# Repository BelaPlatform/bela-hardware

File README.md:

# Bela Hardware

This repo contains the editable hardware design files for Bela products, including Bela, Bela Mini, Bela accessories.

These PCB designs have been created in and are editable with Cadsoft EAGLE (https://cadsoft.io) and Kicad (http://kicad.org). 

## Licensing

The hardware designs in this repo are licensed under a Creative Commons Attribution Sharealike license, or [CC-BY-SA](http://creativecommons.org/licenses/by-sa/3.0/). This means you are free edit and use these designs, as long as you agree to supply credit and release your results under the same license. [Read about CC-BY-SA here](http://creativecommons.org/licenses/by-sa/3.0/).

If you want to create a commercial product using the Bela hardware designs and don't want to release it under the same license, you will need a commercial license. Drop us an email at info@bela.io to discuss your project, and we can suggest a commercial license to fit your project's scope and scale.

## Branding

The Bela logo is copyrighted, and is reserved for products made or licensed by the Bela team. If you want to include a Bela logo on your project, we've made a Made With Bela logo just for this. [See this page for details on logo use](https://belaplatform.github.io/bela_sample/src/#logos) and to download the Made With Bela logo.

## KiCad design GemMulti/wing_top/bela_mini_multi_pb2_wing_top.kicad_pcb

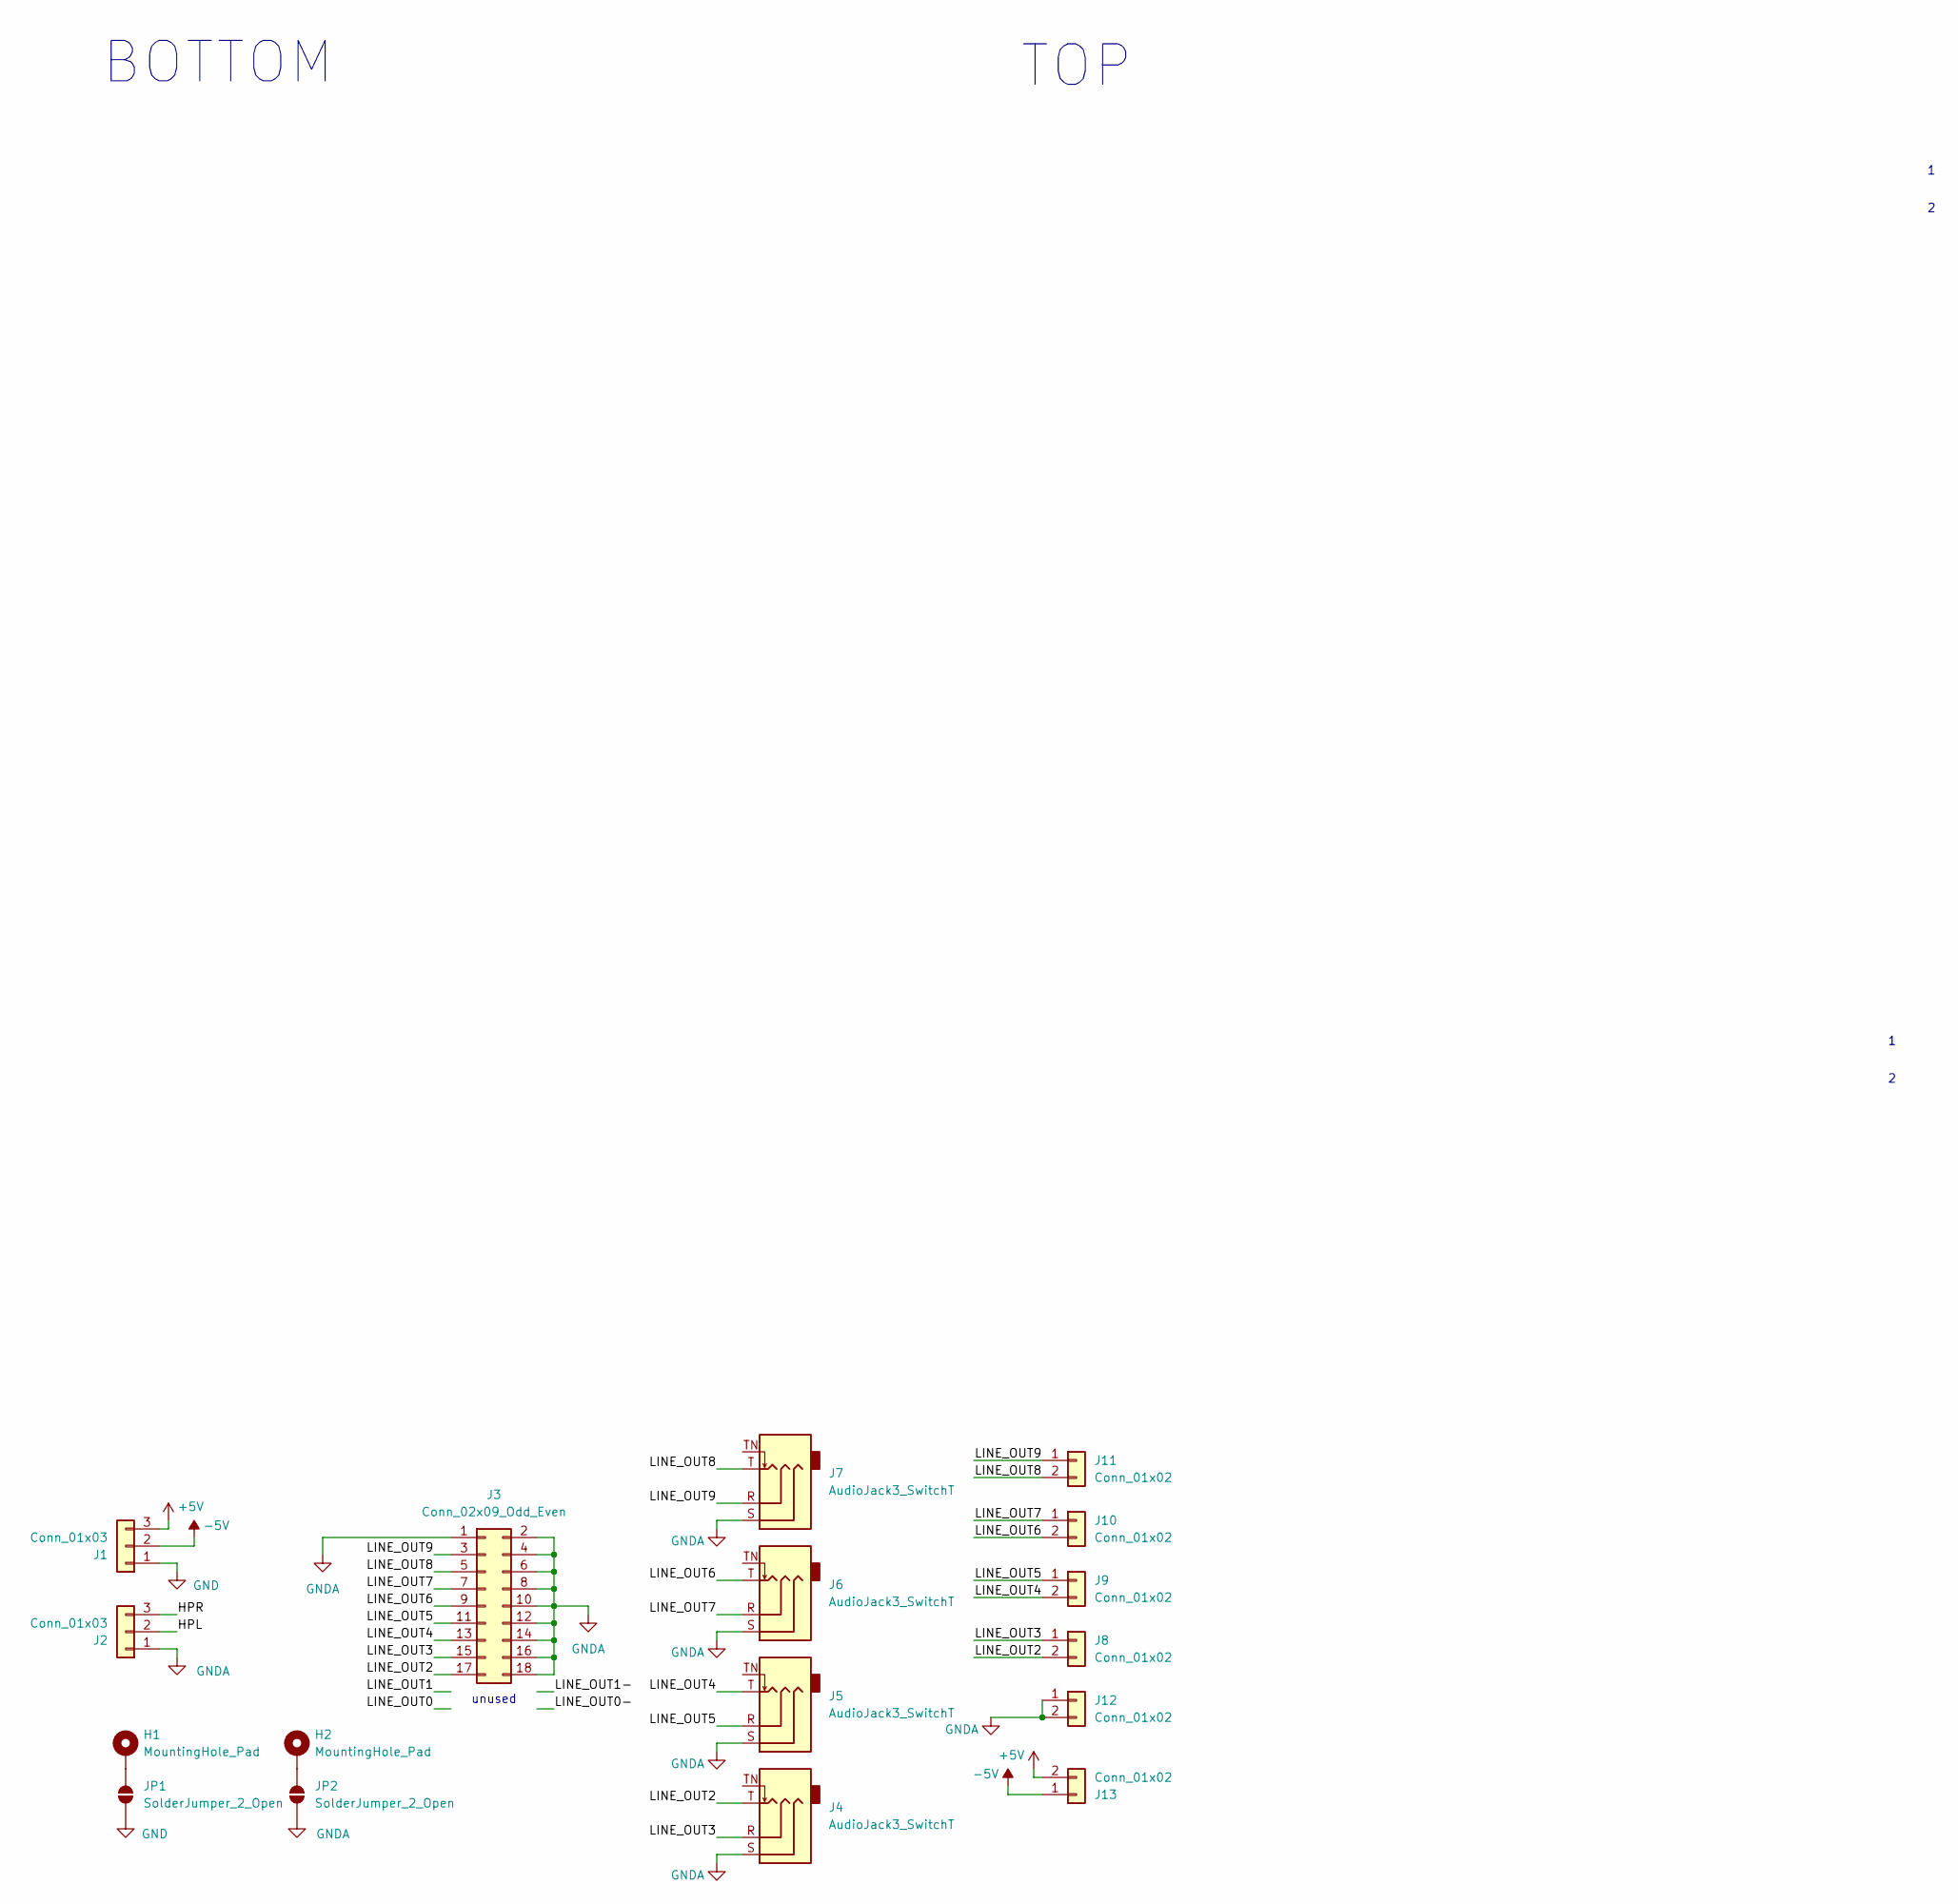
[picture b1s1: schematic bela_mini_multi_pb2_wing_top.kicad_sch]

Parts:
H1, H2: MountingHole_Pad; MountingHole_3.2mm_M3_DIN965_Pad
J1, J2: Conn_01x03; PinHeader_1x03_P2.54mm_Vertical
J3: Conn_02x09_Odd_Even; PinHeader_2x09_P2.54mm_Vertical_SMD
J4, J5, J6, J7: AudioJack3_SwitchT; Jack_3.5mm_SameSky_SJ235813BSMTTR
J8, J9, J10, J11, J12, J13: Conn_01x02; PinSocket_1x02_P2.54mm_Vertical
JP1, JP2: SolderJumper_2_Open; SolderJumper-2_P1.3mm_Open_RoundedPad1.0x1.5mm

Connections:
+5V: J1.3, J13.2
-5V: J1.2, J13.1
/HPL: J2.2
/HPR: J2.3
/LINE_OUT2: J3.17, J4.T, J8.2
/LINE_OUT3: J3.15, J4.R, J8.1
/LINE_OUT4: J3.13, J5.T, J9.2
/LINE_OUT5: J3.11, J5.R, J9.1
/LINE_OUT6: J3.9, J6.T, J10.2
/LINE_OUT7: J3.7, J6.R, J10.1
/LINE_OUT8: J3.5, J7.T, J11.2
/LINE_OUT9: J3.3, J7.R, J11.1
GND: J1.1, JP1.1 (A)
GNDA: J2.1, J3.1, J3.2, J3.4, J3.6, J3.8, J3.10, J3.12, J3.14, J3.16, J3.18, J4.S, J5.S, J6.S, J7.S, J12.1, J12.2, JP2.1 (A)
unnamed: H1.1, JP1.2 (B)
unnamed: H2.1, JP2.2 (B)

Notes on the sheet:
unused
BOTTOM
TOP

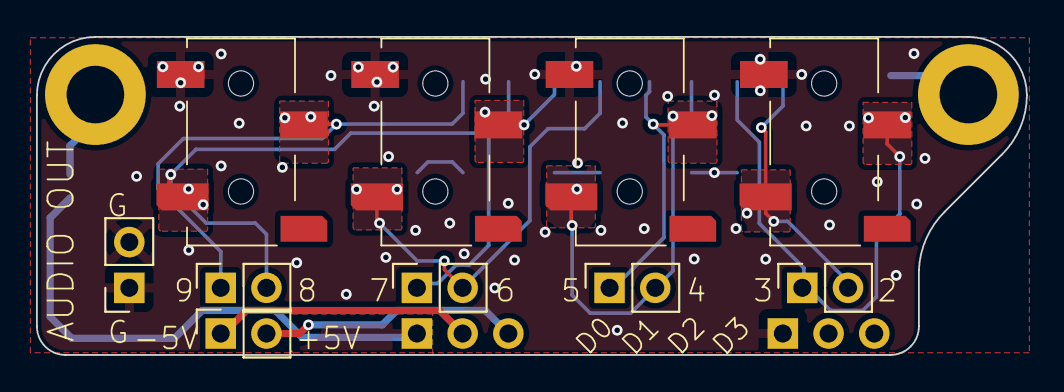
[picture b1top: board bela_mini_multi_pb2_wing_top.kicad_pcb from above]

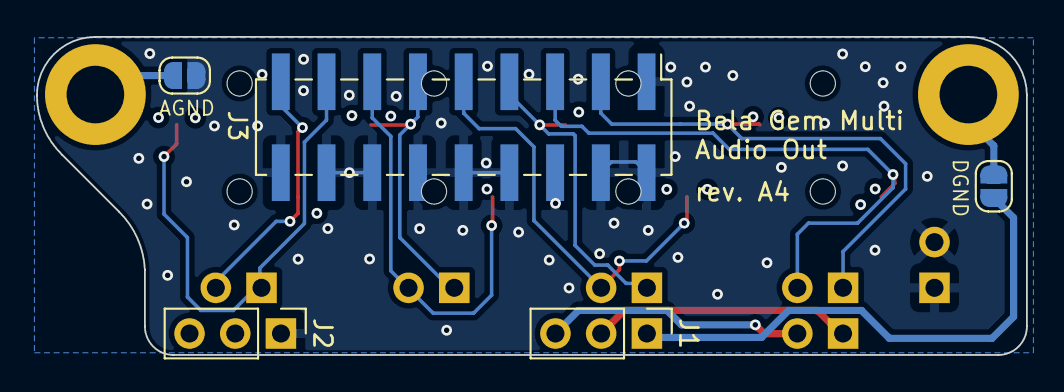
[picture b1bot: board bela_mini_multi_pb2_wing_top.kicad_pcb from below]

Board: 2 copper layers, 55.0 x 17.7 mm, 17 parts (5 on the bottom side), 14 nets.

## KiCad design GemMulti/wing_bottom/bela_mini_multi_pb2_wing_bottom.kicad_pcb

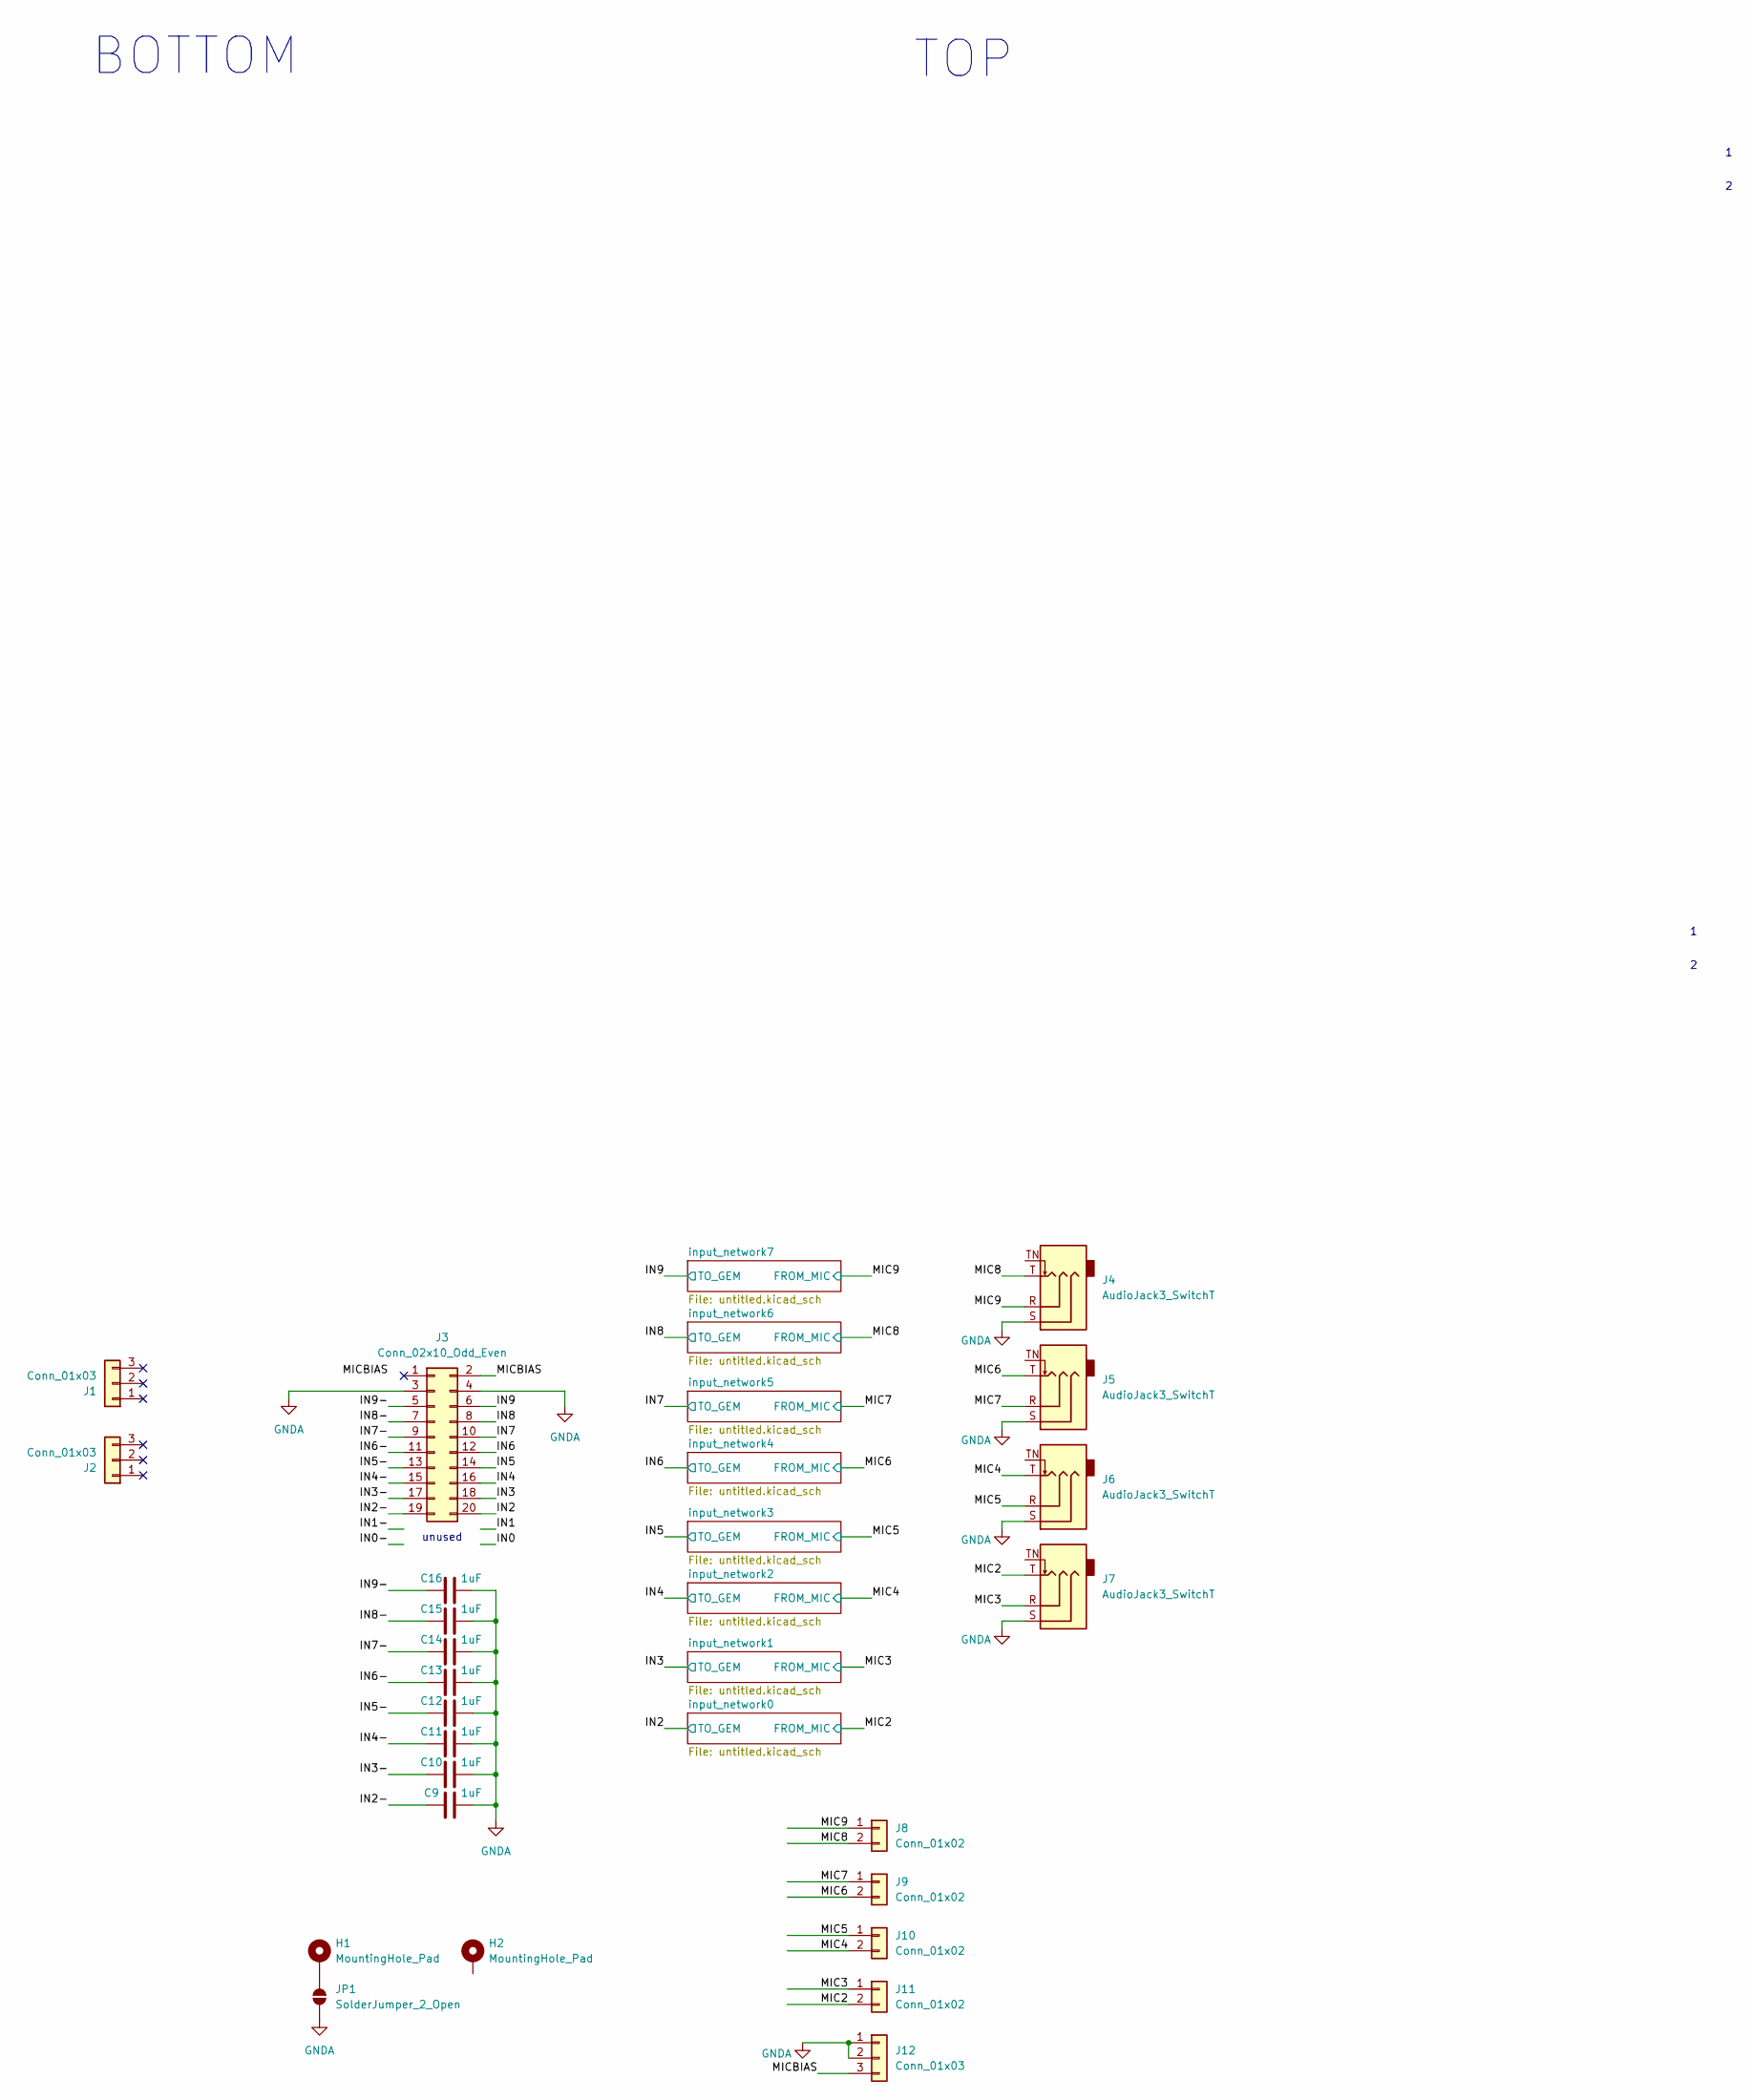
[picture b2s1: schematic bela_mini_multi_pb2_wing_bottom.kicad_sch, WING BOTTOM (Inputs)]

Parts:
C9, C10, C11, C12, C13, C14, C15, C16: 1uF; C_0402_1005Metric
H1, H2: MountingHole_Pad; MountingHole_3.2mm_M3_DIN965_Pad
J1, J2: Conn_01x03; PinHeader_1x03_P2.54mm_Vertical
J3: Conn_02x10_Odd_Even; PinHeader_2x10_P2.54mm_Vertical_SMD
J4, J5, J6, J7: AudioJack3_SwitchT; Jack_3.5mm_SameSky_SJ235813BSMTTR
J8, J9, J10, J11: Conn_01x02; PinSocket_1x02_P2.54mm_Vertical
J12: Conn_01x03; PinSocket_1x03_P2.54mm_Vertical
JP1: SolderJumper_2_Open; SolderJumper-2_P1.3mm_Open_RoundedPad1.0x1.5mm

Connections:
/IN2: J3.20; also elsewhere on the board
/IN2-: C9.1, J3.19
/IN3: J3.18; also elsewhere on the board
/IN3-: C10.1, J3.17
/IN4: J3.16; also elsewhere on the board
/IN4-: C11.1, J3.15
/IN5: J3.14; also elsewhere on the board
/IN5-: C12.1, J3.13
/IN6: J3.12; also elsewhere on the board
/IN6-: C13.1, J3.11
/IN7: J3.10; also elsewhere on the board
/IN7-: C14.1, J3.9
/IN8: J3.8; also elsewhere on the board
/IN8-: C15.1, J3.7
/IN9: J3.6; also elsewhere on the board
/IN9-: C16.1, J3.5
/MIC2: J7.T, J11.2; also elsewhere on the board
/MIC3: J7.R, J11.1; also elsewhere on the board
/MIC4: J6.T, J10.2; also elsewhere on the board
/MIC5: J6.R, J10.1; also elsewhere on the board
/MIC6: J5.T, J9.2; also elsewhere on the board
/MIC7: J5.R, J9.1; also elsewhere on the board
/MIC8: J4.T, J8.2; also elsewhere on the board
/MIC9: J4.R, J8.1; also elsewhere on the board
/MICBIAS: J3.2, J12.3
GNDA: C9.2, C10.2, C11.2, C12.2, C13.2, C14.2, C15.2, C16.2, J3.3, J3.4, J4.S, J5.S, J6.S, J7.S, J12.1, J12.2, JP1.1 (A)
unnamed: H1.1, JP1.2 (B)

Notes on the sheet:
BOTTOM
unused
TOP

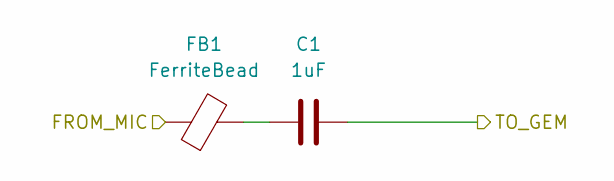
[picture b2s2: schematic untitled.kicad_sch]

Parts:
C1: 1uF; C_0402_1005Metric
FB1: FerriteBead; L_0402_1005Metric

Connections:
/IN2: C1.2; also elsewhere on the board
/MIC2: FB1.1; also elsewhere on the board
unnamed: C1.1, FB1.2

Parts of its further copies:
C2, C3, C4, C5, C6, C7, C8: 1uF; C_0402_1005Metric
FB2, FB3, FB4, FB5, FB6, FB7, FB8: FerriteBead; L_0402_1005Metric

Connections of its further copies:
/IN3: C2.2; also elsewhere on the board
/IN4: C3.2; also elsewhere on the board
/IN5: C4.2; also elsewhere on the board
/IN6: C5.2; also elsewhere on the board
/IN7: C6.2; also elsewhere on the board
/IN8: C7.2; also elsewhere on the board
/IN9: C8.2; also elsewhere on the board
/MIC3: FB2.1; also elsewhere on the board
/MIC4: FB3.1; also elsewhere on the board
/MIC5: FB4.1; also elsewhere on the board
/MIC6: FB5.1; also elsewhere on the board
/MIC7: FB6.1; also elsewhere on the board
/MIC8: FB7.1; also elsewhere on the board
/MIC9: FB8.1; also elsewhere on the board
unnamed: C2.1, FB2.2
unnamed: C3.1, FB3.2
unnamed: C4.1, FB4.2
unnamed: C5.1, FB5.2
unnamed: C6.1, FB6.2
unnamed: C7.1, FB7.2
unnamed: C8.1, FB8.2

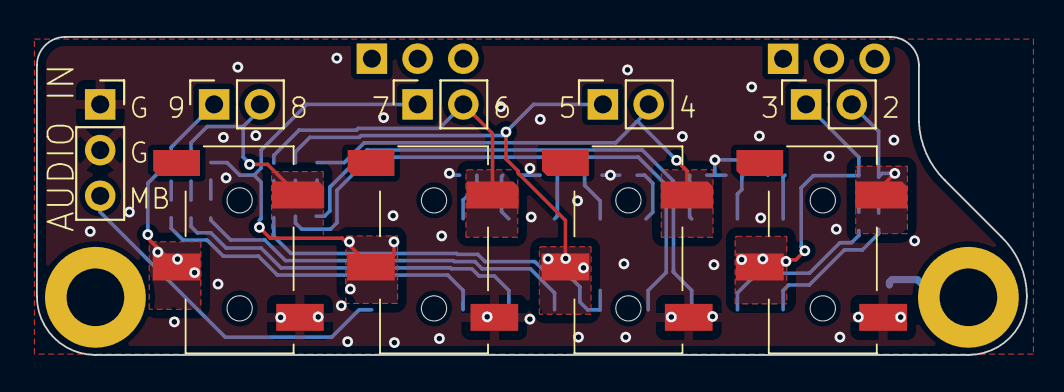
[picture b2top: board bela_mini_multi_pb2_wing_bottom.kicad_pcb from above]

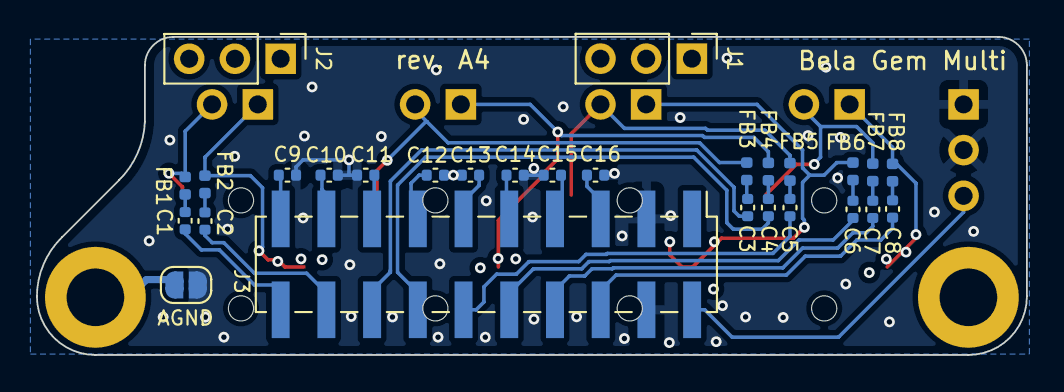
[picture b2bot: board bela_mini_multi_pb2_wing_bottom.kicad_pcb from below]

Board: 2 copper layers, 55.0 x 17.7 mm, 39 parts (28 on the bottom side), 35 nets.

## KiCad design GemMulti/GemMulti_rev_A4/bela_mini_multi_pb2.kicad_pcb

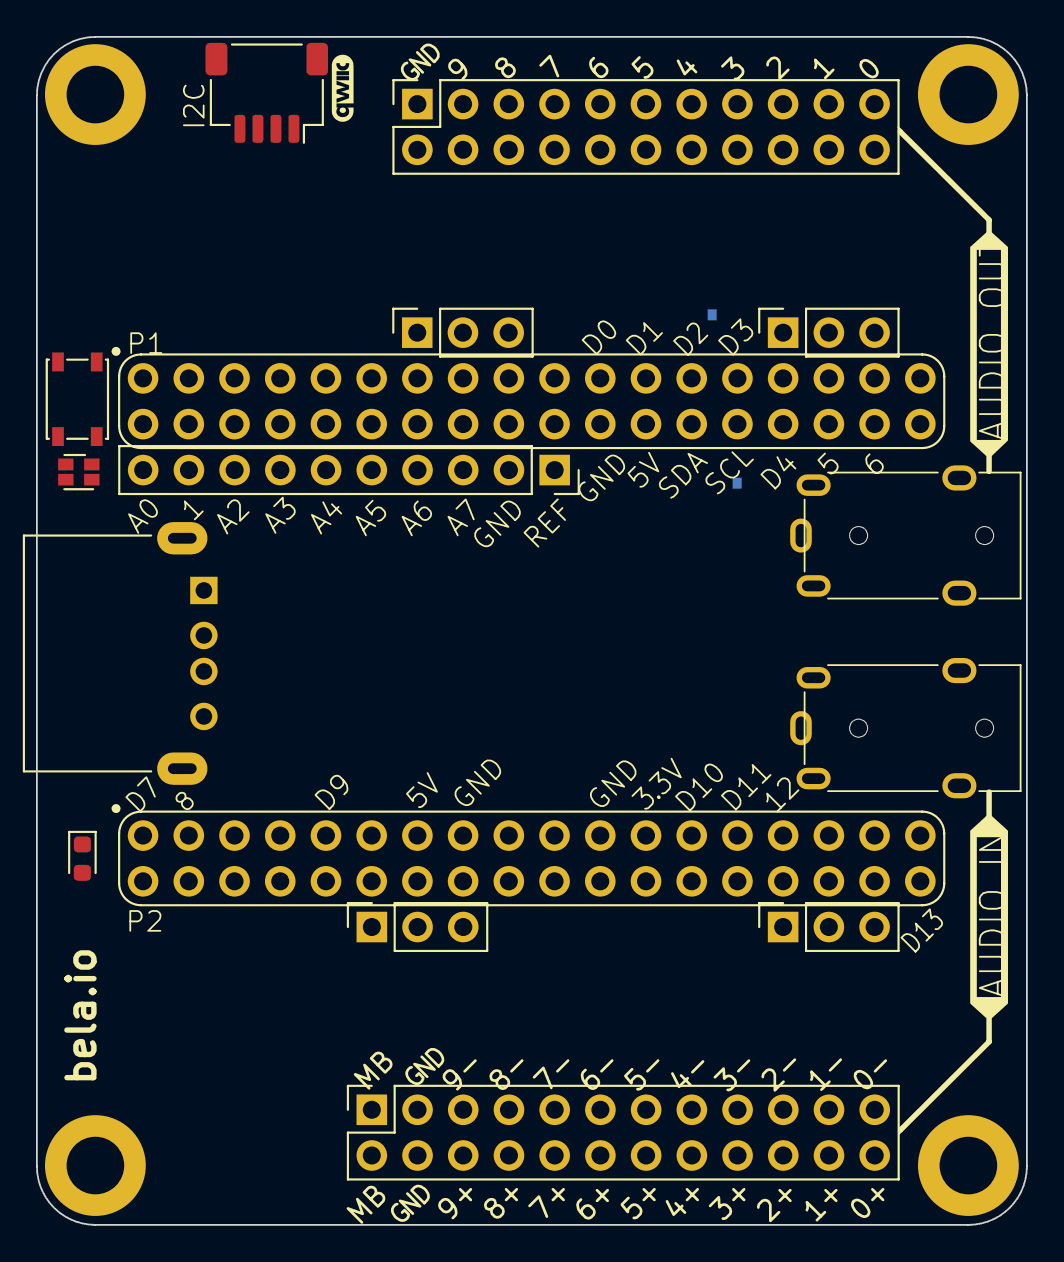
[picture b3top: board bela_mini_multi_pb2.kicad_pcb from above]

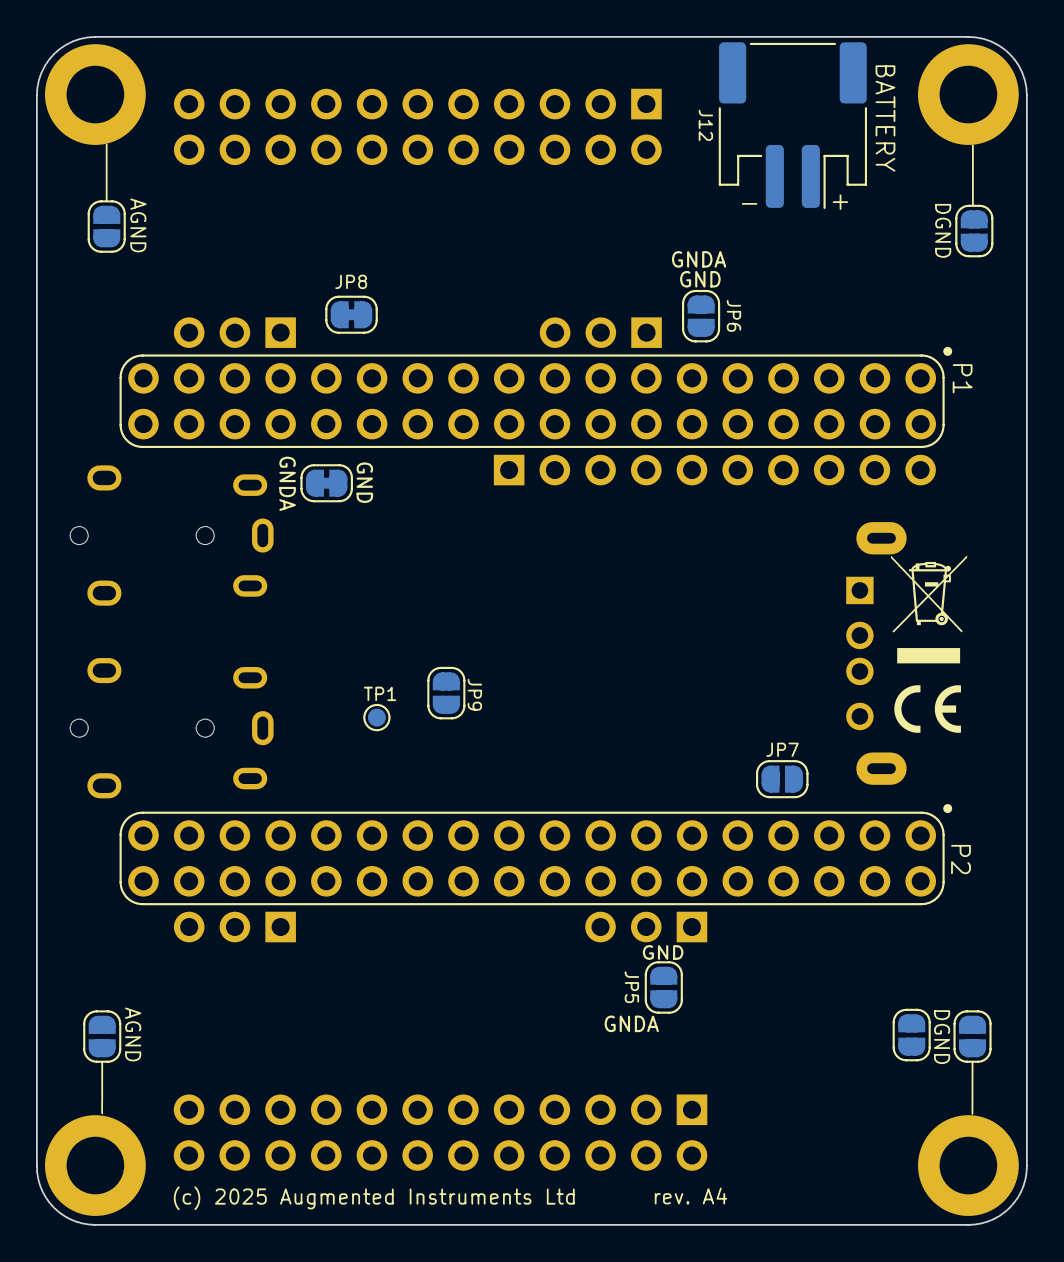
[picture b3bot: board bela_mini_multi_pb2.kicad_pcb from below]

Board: 4 copper layers, 55.0 x 66.0 mm, 34 parts (15 on the bottom side), 21 nets, no tracks yet.

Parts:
D1: LTST-C195TBJRKT; LED_LiteOn_LTST-C19HE1WT
D24: LED; LED_0603_1608Metric
G1: OSHW-Logo; OSHW-Logo2_7.3x6mm_SilkScreen
G3: WEEE-Logo; WEEE-Logo_4.2x6mm_SilkScreen
H1, H2, H3, H4: MountingHole; MountingHole_3.2mm_M3_DIN965_Pad
J1, J2: AudioJack4; Jack_3.5mm_LumbergSubstitute
J3: Conn_01x10; PinSocket_1x10_P2.54mm_Vertical
J4: Conn_01x04_MountingPin; qwiic_horizontal_SMD
J5: USB_A; USB_A_GCT_USB1125
J6: Conn_02x12_Odd_Even; PinSocket_2x12_P2.54mm_Vertical
J7: Conn_02x11_Odd_Even; PinSocket_2x11_P2.54mm_Vertical
J8, J9, J10, J11: Conn_01x03; PinSocket_1x03_P2.54mm_Vertical
J12: Conn_01x02; JST_PH_S2B-PH-SM4-TB_1x02-1MP_P2.00mm_Horizontal
JP1, JP2, JP3, JP4, JP5, JP6, JP7, JP9, JP10: SolderJumper_2_Open; SolderJumper-2_P1.3mm_Open_RoundedPad1.0x1.5mm
JP8: SolderJumper_2_Bridged; SolderJumper-2_P1.3mm_Bridged_RoundedPad1.0x1.5mm
NT1: NetTie_2; SolderJumper-2_P1.3mm_Bridged_RoundedPad1.0x1.5mm
S1: PTS810; SW_SPST_PTS810
TP1: TestPoint; TestPoint_Pad_D1.0mm
U1: PocketBeagle2; PB2

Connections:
+3V3: J4.2, J8.2, JP7.1 (A), U1.P2.23 (3.3V)
+5V: J8.3, J10.3, U1.P1.24 (VOUT), U1.P2.13 (VOUT)
/BAT.VIN: J12.1, U1.P2.14 (BAT.VIN)
/HPL: J2.T, J11.2
/HPR: J2.R1, J11.3
/I2C2.SCL: J4.4, U1.P1.28 (I2C2.SCL)
/I2C2.SDA: J4.3, U1.P1.26 (I2C2.SDA)
/IN0: J1.T, J6.24
/IN1: J1.R1, J6.22
/MICBIAS: J6.1, J6.2
/USBGND: J5.4 (GND), J5.5 (Shield), U1.P1.15 (GND)
/USB_DN: J5.2 (D-), U1.P1.9 (USB1.D-)
/USB_DP: J5.3 (D+), U1.P1.11 (USB1.D+)
/USB_VBUS: J5.1 (VBUS), U1.P1.5 (USB1.VBUS), U1.P1.7 (VIN.USB)
ADC_RST/: JP8.1 (A), U1.P2.18 (GPIO53)
GND: D1.3 (K1), D1.4 (K2), J3.2, J4.1, J4.MP (MountPin), J8.1, J10.1, J12.2, JP1.2 (B), JP3.2 (B), JP5.2 (B), JP6.2 (B), JP10.2 (B), NT1.2, S1.1, U1.P1.16 (GND), U1.P1.22 (GND), U1.P2.15 (GND), U1.P2.21 (GND)
GNDA: J1.R2, J2.R2, J6.3, J6.4, J7.1, J7.2, J7.4, J7.6, J7.8, J7.10, J7.12, J7.14, J7.16, J7.18, J9.1, J9.2, J11.1, JP2.2 (B), JP4.2 (B), JP5.1 (A), JP6.1 (A), NT1.1
unnamed: H1.1, JP1.1 (A)
unnamed: H2.1, JP2.1 (A)
unnamed: H3.1, JP3.1 (A)
unnamed: H4.1, JP4.1 (A)

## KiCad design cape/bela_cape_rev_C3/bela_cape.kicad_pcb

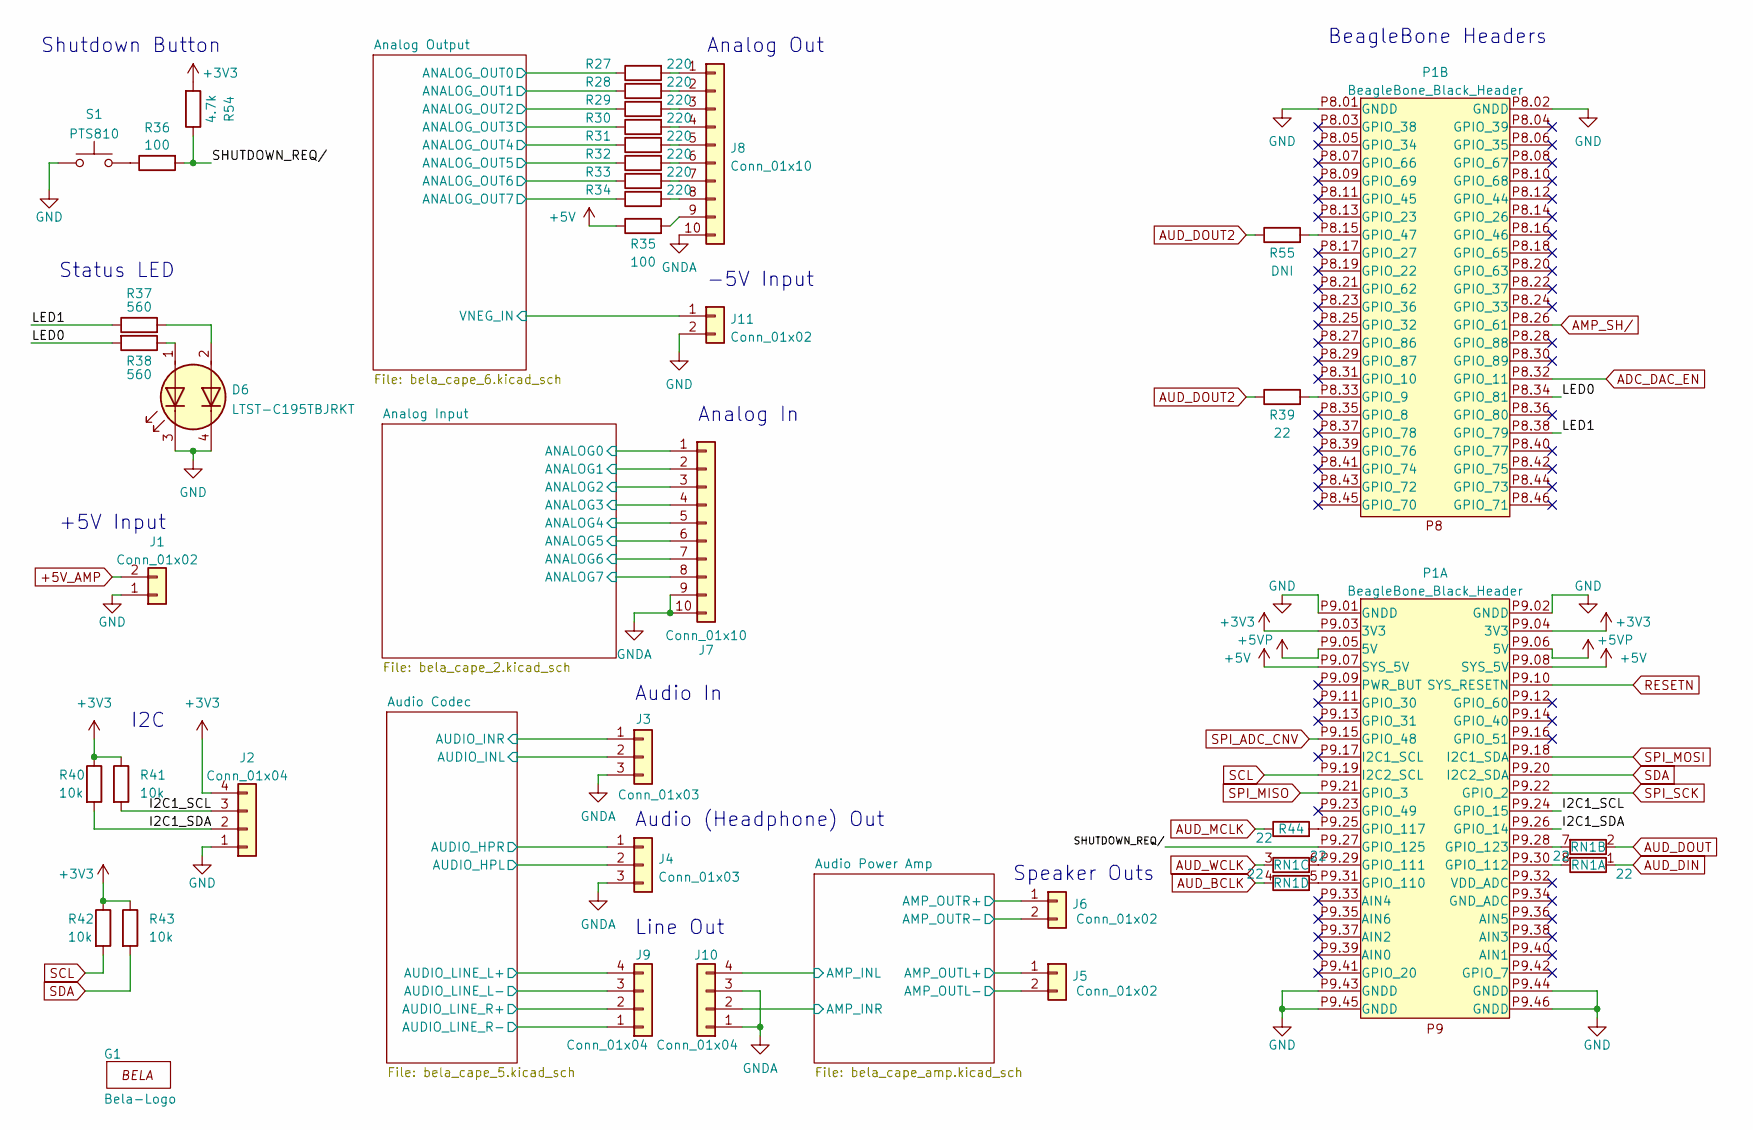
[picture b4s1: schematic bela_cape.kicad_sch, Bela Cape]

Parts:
D6: LTST-C195TBJRKT; LED_LiteOn_LTST-C19HE1WT
G1: Bela-Logo; Bela-Logo_30mm_Silkscreen
J1, J11: Conn_01x02; PinHeader_1x02_P2.54mm_Vertical
J2: Conn_01x04; Molex_KK-254_AE-6410-04A_1x04_P2.54mm_Vertical
J3, J4: Conn_01x03; Molex_KK-254_AE-6410-03A_1x03_P2.54mm_Vertical
J5, J6: Conn_01x02; Molex_KK-254_AE-6410-02A_1x02_P2.54mm_Vertical
J7, J8: Conn_01x10; PinHeader_1x10_P2.54mm_Vertical
J9, J10: Conn_01x04; PinHeader_1x04_P2.54mm_Vertical
P1: BeagleBone_Black_Header; BeagleBone_Black_Sockets_Board_outline
R27, R28, R29, R30, R31, R32, R33, R34: 220; R_0603_1608Metric
R35, R36: 100; R_0603_1608Metric
R37, R38: 560; R_0603_1608Metric
R39, R44: 22; R_0603_1608Metric
R40, R41, R42, R43: 10k; R_0603_1608Metric
R54: 4.7k; R_0603_1608Metric
R55: DNI; R_0603_1608Metric
RN1: 22; R_Array_Convex_4x0603
S1: PTS810; SW_SPST_PTS810

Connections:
+3V3: J2.4, P1.P9.03 (3V3), P1.P9.04 (3V3), R40.1, R41.1, R42.1, R43.1, R54.2; also elsewhere on the board
+5V: P1.P9.07 (SYS_5V), P1.P9.08 (SYS_5V), R35.1; also elsewhere on the board
+5VP: P1.P9.05 (5V), P1.P9.06 (5V); also elsewhere on the board
+5V_AMP: J1.2; also elsewhere on the board
/Analog Input/ANALOG0: J7.1; also elsewhere on the board
/Analog Input/ANALOG1: J7.2; also elsewhere on the board
/Analog Input/ANALOG2: J7.3; also elsewhere on the board
/Analog Input/ANALOG3: J7.4; also elsewhere on the board
/Analog Input/ANALOG4: J7.5; also elsewhere on the board
/Analog Input/ANALOG5: J7.6; also elsewhere on the board
/Analog Input/ANALOG6: J7.7; also elsewhere on the board
/Analog Input/ANALOG7: J7.8; also elsewhere on the board
/Analog Output/ANALOG_OUT0: R27.1; also elsewhere on the board
/Analog Output/ANALOG_OUT1: R28.1; also elsewhere on the board
/Analog Output/ANALOG_OUT2: R29.1; also elsewhere on the board
/Analog Output/ANALOG_OUT3: R30.1; also elsewhere on the board
/Analog Output/ANALOG_OUT4: R31.1; also elsewhere on the board
/Analog Output/ANALOG_OUT5: R32.1; also elsewhere on the board
/Analog Output/ANALOG_OUT6: R33.1; also elsewhere on the board
/Analog Output/ANALOG_OUT7: R34.1; also elsewhere on the board
/Analog Output/VNEG_IN: J11.1; also elsewhere on the board
/Audio Codec/AUDIO_HPL: J4.2; also elsewhere on the board
/Audio Codec/AUDIO_HPR: J4.1; also elsewhere on the board
/Audio Codec/AUDIO_INL: J3.2; also elsewhere on the board
/Audio Codec/AUDIO_INR: J3.1; also elsewhere on the board
/Audio Codec/AUDIO_LINE_L+: J9.4; also elsewhere on the board
/Audio Codec/AUDIO_LINE_L-: J9.3; also elsewhere on the board
/Audio Codec/AUDIO_LINE_R+: J9.2; also elsewhere on the board
/Audio Codec/AUDIO_LINE_R-: J9.1; also elsewhere on the board
/Audio Power Amp/AMP_INL: J10.4; also elsewhere on the board
/Audio Power Amp/AMP_INR: J10.2; also elsewhere on the board
/Audio Power Amp/AMP_OUTL+: J5.1; also elsewhere on the board
/Audio Power Amp/AMP_OUTL-: J5.2; also elsewhere on the board
/Audio Power Amp/AMP_OUTR+: J6.1; also elsewhere on the board
/Audio Power Amp/AMP_OUTR-: J6.2; also elsewhere on the board
/I2C1_SCL: J2.3, P1.P9.24 (GPIO_15), R41.2
/I2C1_SDA: J2.2, P1.P9.26 (GPIO_14), R40.2
/LED0: P1.P8.34 (GPIO_81), R38.2
/LED1: P1.P8.38 (GPIO_79), R37.1
/SHUTDOWN_REQ/: P1.P9.27 (GPIO_125), R36.2, R54.1
ADC_DAC_EN: P1.P8.32 (GPIO_11); also elsewhere on the board
AMP_SH/: P1.P8.26 (GPIO_61); also elsewhere on the board
AUD_BCLK: RN1.4 (R4.1); also elsewhere on the board
AUD_DIN: RN1.1 (R1.1); also elsewhere on the board
AUD_DOUT: RN1.2 (R2.1); also elsewhere on the board
AUD_DOUT2: R39.1, R55.1; also elsewhere on the board
AUD_MCLK: R44.1; also elsewhere on the board
AUD_WCLK: RN1.3 (R3.1); also elsewhere on the board
GND: D6.3 (K1), D6.4 (K2), J1.1, J2.1, J11.2, P1.P8.01 (GNDD), P1.P8.02 (GNDD), P1.P9.01 (GNDD), P1.P9.02 (GNDD), P1.P9.43 (GNDD), P1.P9.44 (GNDD), P1.P9.45 (GNDD), P1.P9.46 (GNDD), S1.2; also elsewhere on the board
GNDA: J3.3, J4.3, J7.9, J7.10, J8.10, J10.1, J10.3; also elsewhere on the board
unnamed: D6.1 (A1), R38.1
unnamed: D6.2 (A2), R37.2
unnamed: J8.1, R27.2
unnamed: J8.2, R28.2
unnamed: J8.3, R29.2
unnamed: J8.4, R30.2
unnamed: J8.5, R31.2
unnamed: J8.6, R32.2
unnamed: J8.7, R33.2
unnamed: J8.8, R34.2
unnamed: J8.9, R35.2
unnamed: P1.P8.15 (GPIO_47), R55.2
unnamed: P1.P8.33 (GPIO_9), R39.2
unnamed: P1.P9.25 (GPIO_117), R44.2
unnamed: P1.P9.28 (GPIO_123), RN1.7 (R2.2)
unnamed: P1.P9.29 (GPIO_111), RN1.6 (R3.2)
unnamed: P1.P9.30 (GPIO_112), RN1.8 (R1.2)
unnamed: P1.P9.31 (GPIO_110), RN1.5 (R4.2)
unnamed: R36.1, S1.1
RESETN: P1.P9.10 (SYS_RESETN); also elsewhere on the board
SCL: P1.P9.19 (I2C2_SCL), R42.2; also elsewhere on the board
SDA: P1.P9.20 (I2C2_SDA), R43.2; also elsewhere on the board
SPI_ADC_CNV: P1.P9.15 (GPIO_48); also elsewhere on the board
SPI_MISO: P1.P9.21 (GPIO_3); also elsewhere on the board
SPI_MOSI: P1.P9.18 (I2C1_SDA); also elsewhere on the board
SPI_SCK: P1.P9.22 (GPIO_2); also elsewhere on the board

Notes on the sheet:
Audio (Headphone) Out
Analog Out
I2C
Audio In
BeagleBone Headers
Analog In
Status LED
-5V Input
Shutdown Button
+5V Input
Line Out
Speaker Outs

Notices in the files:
GemMulti/GemMulti_rev_A4/bela_mini_multi_pb2.kicad_pcb:
(c) 2025 Augmented Instruments Ltd
